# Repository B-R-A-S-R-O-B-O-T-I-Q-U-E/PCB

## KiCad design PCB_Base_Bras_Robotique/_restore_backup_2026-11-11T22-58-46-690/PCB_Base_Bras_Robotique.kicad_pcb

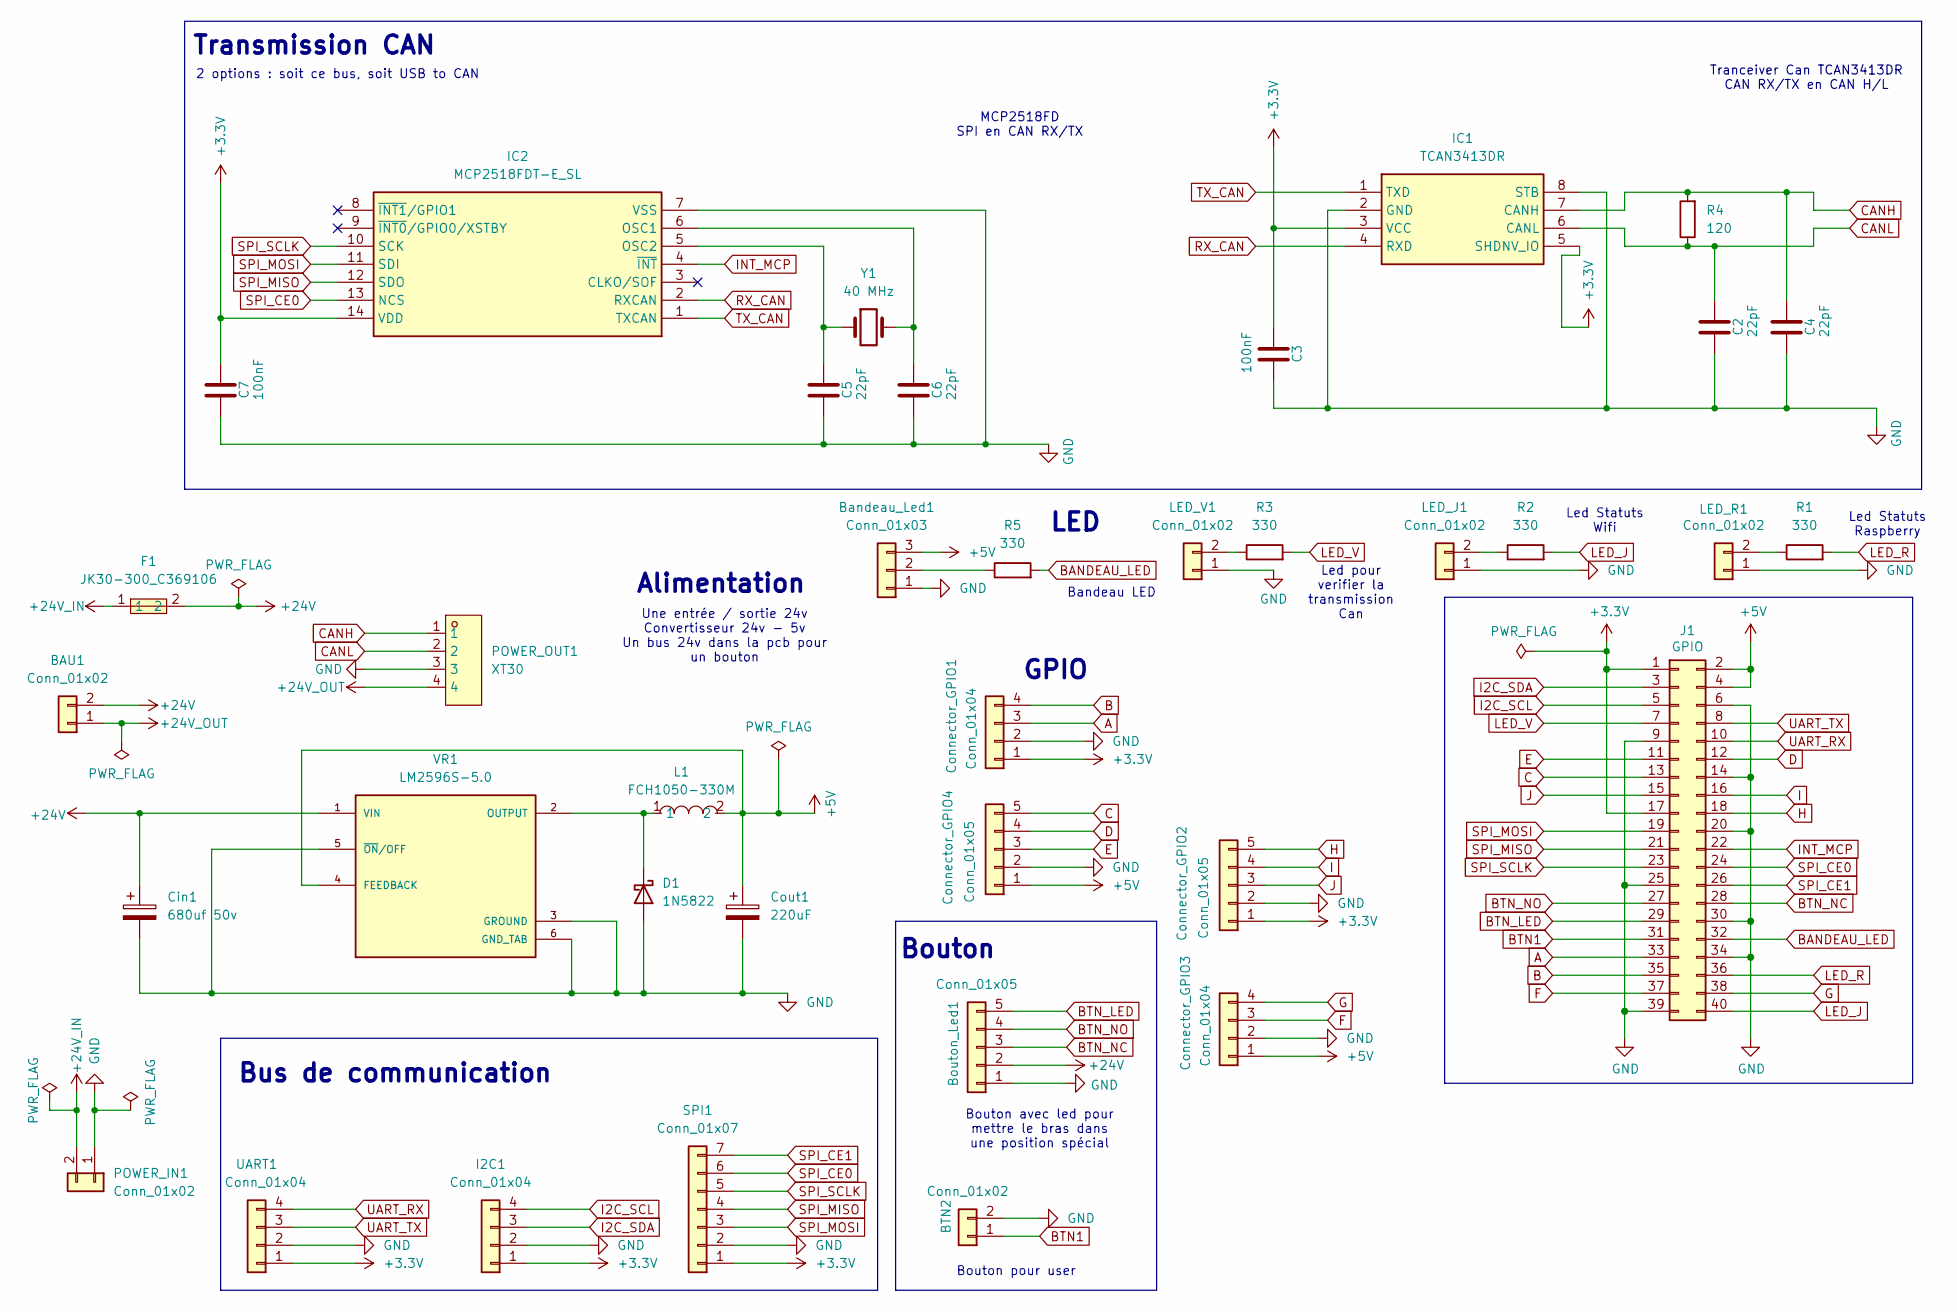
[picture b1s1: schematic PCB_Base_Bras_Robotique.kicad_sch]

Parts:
BAU1: Conn_01x02; TerminalBlock_Phoenix_MKDS-1,5-2_1x02_P5.00mm_Horizontal
BTN2: Conn_01x02; PinHeader_1x02_P2.54mm_Vertical
Bandeau_Led1: Conn_01x03; PinHeader_1x03_P2.54mm_Vertical
Bouton_Led1: Conn_01x05; PinHeader_1x05_P2.54mm_Vertical
C2, C4, C5, C6: 22pF; C_0603_1608Metric
C3, C7: 100nF; C_0603_1608Metric
Cin1: 680uf 50v; CP_Radial_D13.0mm_P5.00mm
Connector_GPIO1, Connector_GPIO3: Conn_01x04; PinHeader_1x04_P2.54mm_Vertical
Connector_GPIO2, Connector_GPIO4: Conn_01x05; PinHeader_1x05_P2.54mm_Vertical
Cout1: 220uF; CP_Radial_D6.3mm_P2.50mm
D1: 1N5822; D_DO-201AD_P15.24mm_Horizontal
F1: JK30-300_C369106; FUSE-TH_L13.0-W3.1-P5.08-D1.2; MPN JK30-300; LCSC Part C369106
I2C1: Conn_01x04; PinHeader_1x04_P2.54mm_Vertical
IC1: TCAN3413DR; SOIC127P600X175-8N; Manufacturer_Part_Number TCAN3413DR; Mouser Part Number 595-TCAN3413DR
IC2: MCP2518FDT-E_SL; SOIC127P600X175-14N; Manufacturer_Part_Number MCP2518FDT-E/SL; Mouser Part Number 579-MCP2518FDT-E/SL
J1: GPIO; PinSocket_2x20_P2.54mm_Vertical
L1: FCH1050-330M; C20415549; MPN FCH1050-330M; LCSC Part C20415549
LED_J1: Conn_01x02; PinHeader_1x02_P2.54mm_Vertical
LED_R1: Conn_01x02; PinHeader_1x02_P2.54mm_Vertical
LED_V1: Conn_01x02; PinHeader_1x02_P2.54mm_Vertical
POWER_IN1: Conn_01x02; AMASS_XT30U-M_1x02_P5.0mm_Vertical
POWER_OUT1: XT30; CONN-TH_XT30PB-M; MPN XT30(2+2)PB-M.G.B; LCSC Part C19268029
R1, R2, R3, R5: 330; R_0603_1608Metric
R4: 120; R_0603_1608Metric
SPI1: Conn_01x07; PinHeader_1x07_P2.54mm_Vertical
UART1: Conn_01x04; PinHeader_1x04_P2.54mm_Vertical
VR1: LM2596S-5.0; TO170P1524X483-6N; MPN LM2596S-5.0
Y1: 40 MHz; Crystal_SMD_3225-4Pin_3.2x2.5mm

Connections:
+3.3V: C3.1, C7.1, Connector_GPIO1.1, Connector_GPIO2.1, I2C1.1, IC1.3 (VCC), IC1.5 (SHDNV_IO), IC2.14 (VDD), J1.1, J1.17, SPI1.1, UART1.1
+5V: Bandeau_Led1.3, Connector_GPIO3.1, Connector_GPIO4.1, Cout1.1, J1.2, J1.4, L1.2, VR1.4 (FEEDBACK)
+24V: BAU1.2, Bouton_Led1.2, Cin1.1, F1.2, VR1.1 (VIN)
+24V_IN: F1.1, POWER_IN1.2
+24V_OUT: BAU1.1, POWER_OUT1.4
A: Connector_GPIO1.3, J1.33
B: Connector_GPIO1.4, J1.35
BANDEAU_LED: J1.32, R5.2
BTN1: BTN2.1, J1.31
BTN_LED: Bouton_Led1.5, J1.29
BTN_NC: Bouton_Led1.3, J1.28
BTN_NO: Bouton_Led1.4, J1.27
C: Connector_GPIO4.5, J1.13
CANH: C4.1, IC1.7 (CANH), POWER_OUT1.1, R4.2
CANL: C2.1, IC1.6 (CANL), POWER_OUT1.2, R4.1
D: Connector_GPIO4.4, J1.12
E: Connector_GPIO4.3, J1.11
F: Connector_GPIO3.3, J1.37
G: Connector_GPIO3.4, J1.38
GND: BTN2.2, Bandeau_Led1.1, Bouton_Led1.1, C2.2, C3.2, C4.2, C5.2, C6.2, C7.2, Cin1.2, Connector_GPIO1.2, Connector_GPIO2.2, Connector_GPIO3.2, Connector_GPIO4.2, Cout1.2, D1.2 (A), I2C1.2, IC1.2 (GND), IC1.8 (STB), IC2.7 (VSS), J1.6, J1.9, J1.14, J1.20, J1.25, J1.30, J1.34, J1.39, LED_J1.1, LED_R1.1, LED_V1.1, POWER_IN1.1, POWER_OUT1.3, SPI1.2, UART1.2, VR1.3 (GROUND), VR1.5 (~ON/OFF), VR1.6 (GND_TAB)
H: Connector_GPIO2.5, J1.18
I: Connector_GPIO2.4, J1.16
I2C_SCL: I2C1.4, J1.5
I2C_SDA: I2C1.3, J1.3
INT_MCP: IC2.4 (~INT), J1.22
J: Connector_GPIO2.3, J1.15
LED_J: J1.40, R2.2
LED_R: J1.36, R1.2
LED_V: J1.7, R3.2
unnamed: Bandeau_Led1.2, R5.1
unnamed: D1.1 (K), L1.1, VR1.2 (OUTPUT)
unnamed: C6.1, IC2.6 (OSC1), Y1.2
unnamed: C5.1, IC2.5 (OSC2), Y1.1
unnamed: LED_J1.2, R2.1
unnamed: LED_R1.2, R1.1
unnamed: LED_V1.2, R3.1
RX_CAN: IC1.4 (RXD), IC2.2 (RXCAN)
SPI_CE0: IC2.13 (NCS), J1.24, SPI1.6
SPI_CE1: J1.26, SPI1.7
SPI_MISO: IC2.12 (SDO), J1.21, SPI1.4
SPI_MOSI: IC2.11 (SDI), J1.19, SPI1.3
SPI_SCLK: IC2.10 (SCK), J1.23, SPI1.5
TX_CAN: IC1.1 (TXD), IC2.1 (TXCAN)
UART_RX: J1.10, UART1.4
UART_TX: J1.8, UART1.3

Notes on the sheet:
GPIO
Led Statuts Wifi
MCP2518FD SPI en CAN RX/TX
Transmission CAN
Bouton
Alimentation
Led pour verifier la transmission Can
Tranceiver Can TCAN3413DR CAN RX/TX en CAN H/L
Led Statuts Raspberry
Bouton avec led pour mettre le bras dans une position spécial
Bandeau LED
Bouton pour user
LED
2 options : soit ce bus, soit USB to CAN
Une entrée / sortie 24v Convertisseur 24v - 5v Un bus 24v dans la pcb pour un bouton
Bus de communication

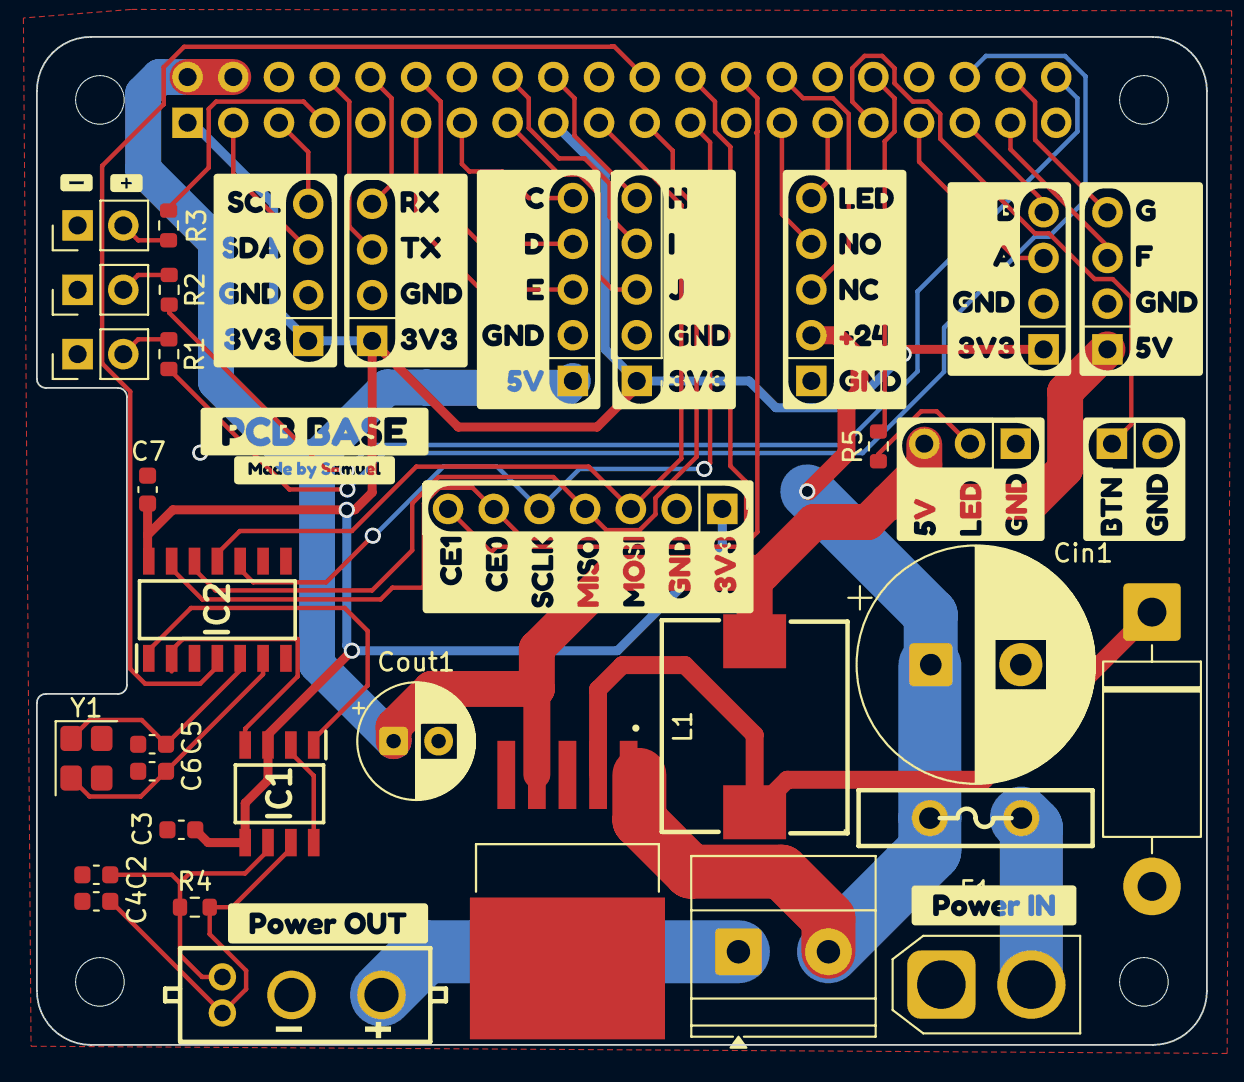
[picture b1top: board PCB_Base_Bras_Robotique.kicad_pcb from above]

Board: 2 copper layers, 65.0 x 56.0 mm, 57 parts (1 on the bottom side), 45 nets.

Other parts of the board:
MH1, MH2, MH3, MH4: MountingHole_2.7mm_M2.5
kobee-studio-6AF39A4C: Kobee Studio; kobee-studio-6AF39A41
kobee-studio-6AF46A8A: Kobee Studio; kobee-studio-6AF46A8A
kobee-studio-6AF46E11: Kobee Studio; kobee-studio-6AF3942E
kobee-studio-6AF47BC9: Kobee Studio; kobee-studio-6AF47B7D
kobee-studio-6AF47BEA: Kobee Studio; kobee-studio-6AF47B94
kobee-studio-6AF47DA9: Kobee Studio; kobee-studio-6AF47D94
kobee-studio-6AF48B4F: Kobee Studio; kobee-studio-6AF39692
kobee-studio-6AF48B35: Kobee Studio; kobee-studio-6AF394EE
kobee-studio-6AF48B44: Kobee Studio; kobee-studio-6AF391BB
kobee-studio-6AF48C1A: Kobee Studio; kobee-studio-6AF475C9
kobee-studio-6AF48C04: Kobee Studio; kobee-studio-6AF39135
kobee-studio-6AF394B5: Kobee Studio; kobee-studio-6AF39169
kobee-studio-6AF469A6: Kobee Studio; kobee-studio-6AF46958
kobee-studio-6AF475AF: Kobee Studio; kobee-studio-6AF475AF
kobee-studio-6AF3948F: Kobee Studio; kobee-studio-6AF3919E
kobee-studio-6AF4771F: Kobee Studio; kobee-studio-6AF47703
